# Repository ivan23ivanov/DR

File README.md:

# Дипломна работа на Иван Иванов 12 Г клас
 # BASS - Bulgarian Automated Smart Sonar, IoT сонар-асистент на риболовеца

## Съдържание:

- Електрическа схема
  - Компоненти:
    - Микроконтролер - Seeed Studio XIAO ESP32C3
    - Ултразвуков сензор за измерване на дълбочината на водния стълб - JSN-SR04T
    - Комбиниран сензор за измерване на температурата на въздуха и атмосферното налягане - BME280
    - Изолоран цифров температурен сензор за измерване температурата на водата DS18B20
      
- Печатна платка
  - Използвана CAD с-ма - KiCad
  - За изработената платка:
    - Два активни слоя
    - Едностранно разположение на компонентите
    - Ширини на пистите - 0.5 мм (сигнални), 1 мм (захранващи)
      
- Управляващ софтуер
  - Среда за разработка - Visual Studio Code
  - Extention - PlatformIO
  - Взимане на входна информация от сензорите и изчисления
  - Изпращане на информацията към мобилното приложение (за Android OS)
  
- Приложен софтуер
  - Android приложение, използващо Flutter framework-а за Android Studio
  - Приложението съдържа:
   - Екран за сканиране за различни BLE устройства
   - Режим "Сурови данни"
   - Режим "Асистент"
   
- Документация
  - Съдържание:
    - Увод
    - Първа глава - Проучване на съществуващи проекти
    - Втора глава - Основни изисквания и блокови схеми
    - Трета глава - Проектиране на принципна електрическа
    - Четвърта глава - Проектиране на печатна платка
    - Пета глава -  Управляващ и приложен софтуер
    - Шеста глава - Практически резултати
    - Заключение

Файловете на печатната платка, електрическата схема, документацията и софтуера могат да бъдат намерени по-горе в repository-то.

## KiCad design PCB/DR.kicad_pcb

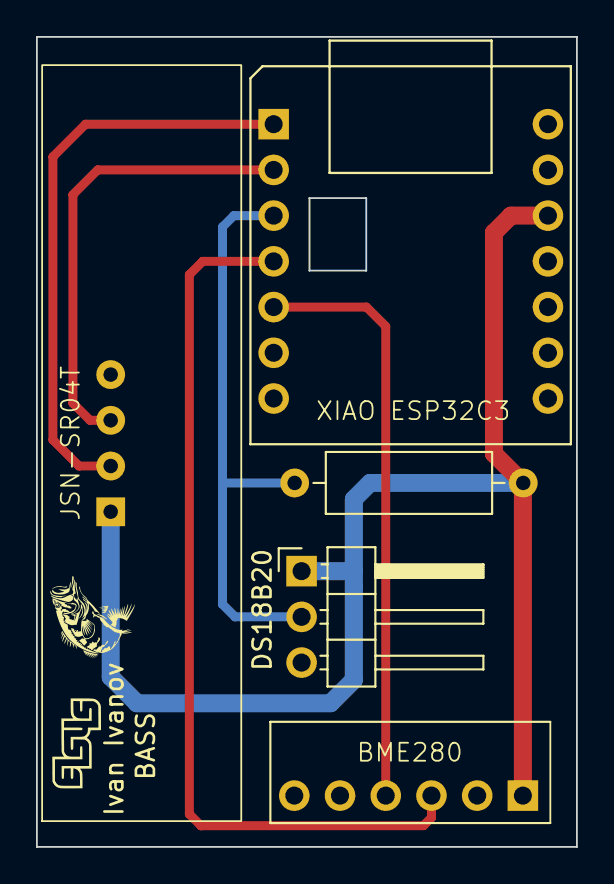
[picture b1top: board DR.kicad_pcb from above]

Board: 2 copper layers, 30.0 x 45.0 mm, 5 parts (0 on the bottom side), 7 nets.

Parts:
R1: 4.7k; R_Axial_DIN0309_L9.0mm_D3.2mm_P12.70mm_Horizontal
U1: XIAO ESP32C3
U2: JSN-SR04T
U3: BME280
U4: 3pin conn

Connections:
+3.3V: R1.2, U1.12 (3V3), U2.1 (VCC), U3.1 (VCC), U4.1 (VDD)
DQ: R1.1, U1.3 (D2), U4.2 (DATA)
Echo: U1.2 (D1), U2.3 (Echo)
GNDD: U1.13 (GND), U2.4 (GND), U3.2 (GND), U4.3 (GND)
SCL: U1.4 (D3), U3.3 (SCL)
SDA: U1.5 (D4), U3.4 (SDA)
Trig: U1.1 (D0), U2.2 (Trig)

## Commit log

2024-02-12 Create Sensors test
    Example code for all sensors
2024-02-12 Create BLE communication, LightBlue
2024-02-12 Create Example code (working)
2024-02-12 Create example code
2024-02-12 Create DS18B20
2024-02-12 Create Combined sensors test
2024-02-12 Create XIAO-LightBlue
2024-02-12 Create ScanForDevices
2024-02-12 Add files via upload
    KiCad files uploaded just in case ;)
2024-02-13 Create JSN-SR04T
2024-02-13 Create Updated pins on sensor test
2024-02-17 Create hihihiha
2024-02-17 Create aaaaaaaaaaaaaa
2024-02-17 App update
2024-02-19 updated app
2024-04-15 App update.
2024-04-17 Added graphs!!!
2024-05-19 Organizing folders
    Making it all look good
